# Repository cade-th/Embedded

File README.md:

# Kitchen Timer: Embedded Systems Project

Cade Thornton

10/23/2023

Embedded Systems

## Table of Contents

-------

+ [Introduction](#Introduction )
+ [PCB Design in KiCad](#PCBDesigninKiCad)
    * [Schematic](#Schematic)
    * [Layout](#Layout)

+ [Arduino Code](#ArduinoCode)
    * [Overview](#Overview)

+ [Conclusion](#Conclusion)

## Introduction 

-------

The goal of this project is to create a PCB schematic and layout for a simple kitchen timer made using the AT-mega microprocessor, the Arduino IDE, and KiCad.

<div align="center">
  <p style="font-size: small;">
    Figure 1 (Completed PCB board setup)
  </p>
</div>

## PCB design in KiCad

### Schematic
<p align="center"> 
The schematic for this design included roughly nine modules that work fit together to make the full system.
</p>

<div align="center">
  <p style="font-size: small;">
    Figure 2 (entire schematic PCB system)
  </p>
</div>

### Layout 

<p align="center"> 
The layout for this design was created after finishing the schematic design. 
</p>

<div align="center">
  <p style="font-size: small;">
    Figure 2 (entire layout of the PCB system)
  </p>
</div>

------

## Arduino Code

The code used to program the kitchen timer can be found in the /ArduinoCode folder.

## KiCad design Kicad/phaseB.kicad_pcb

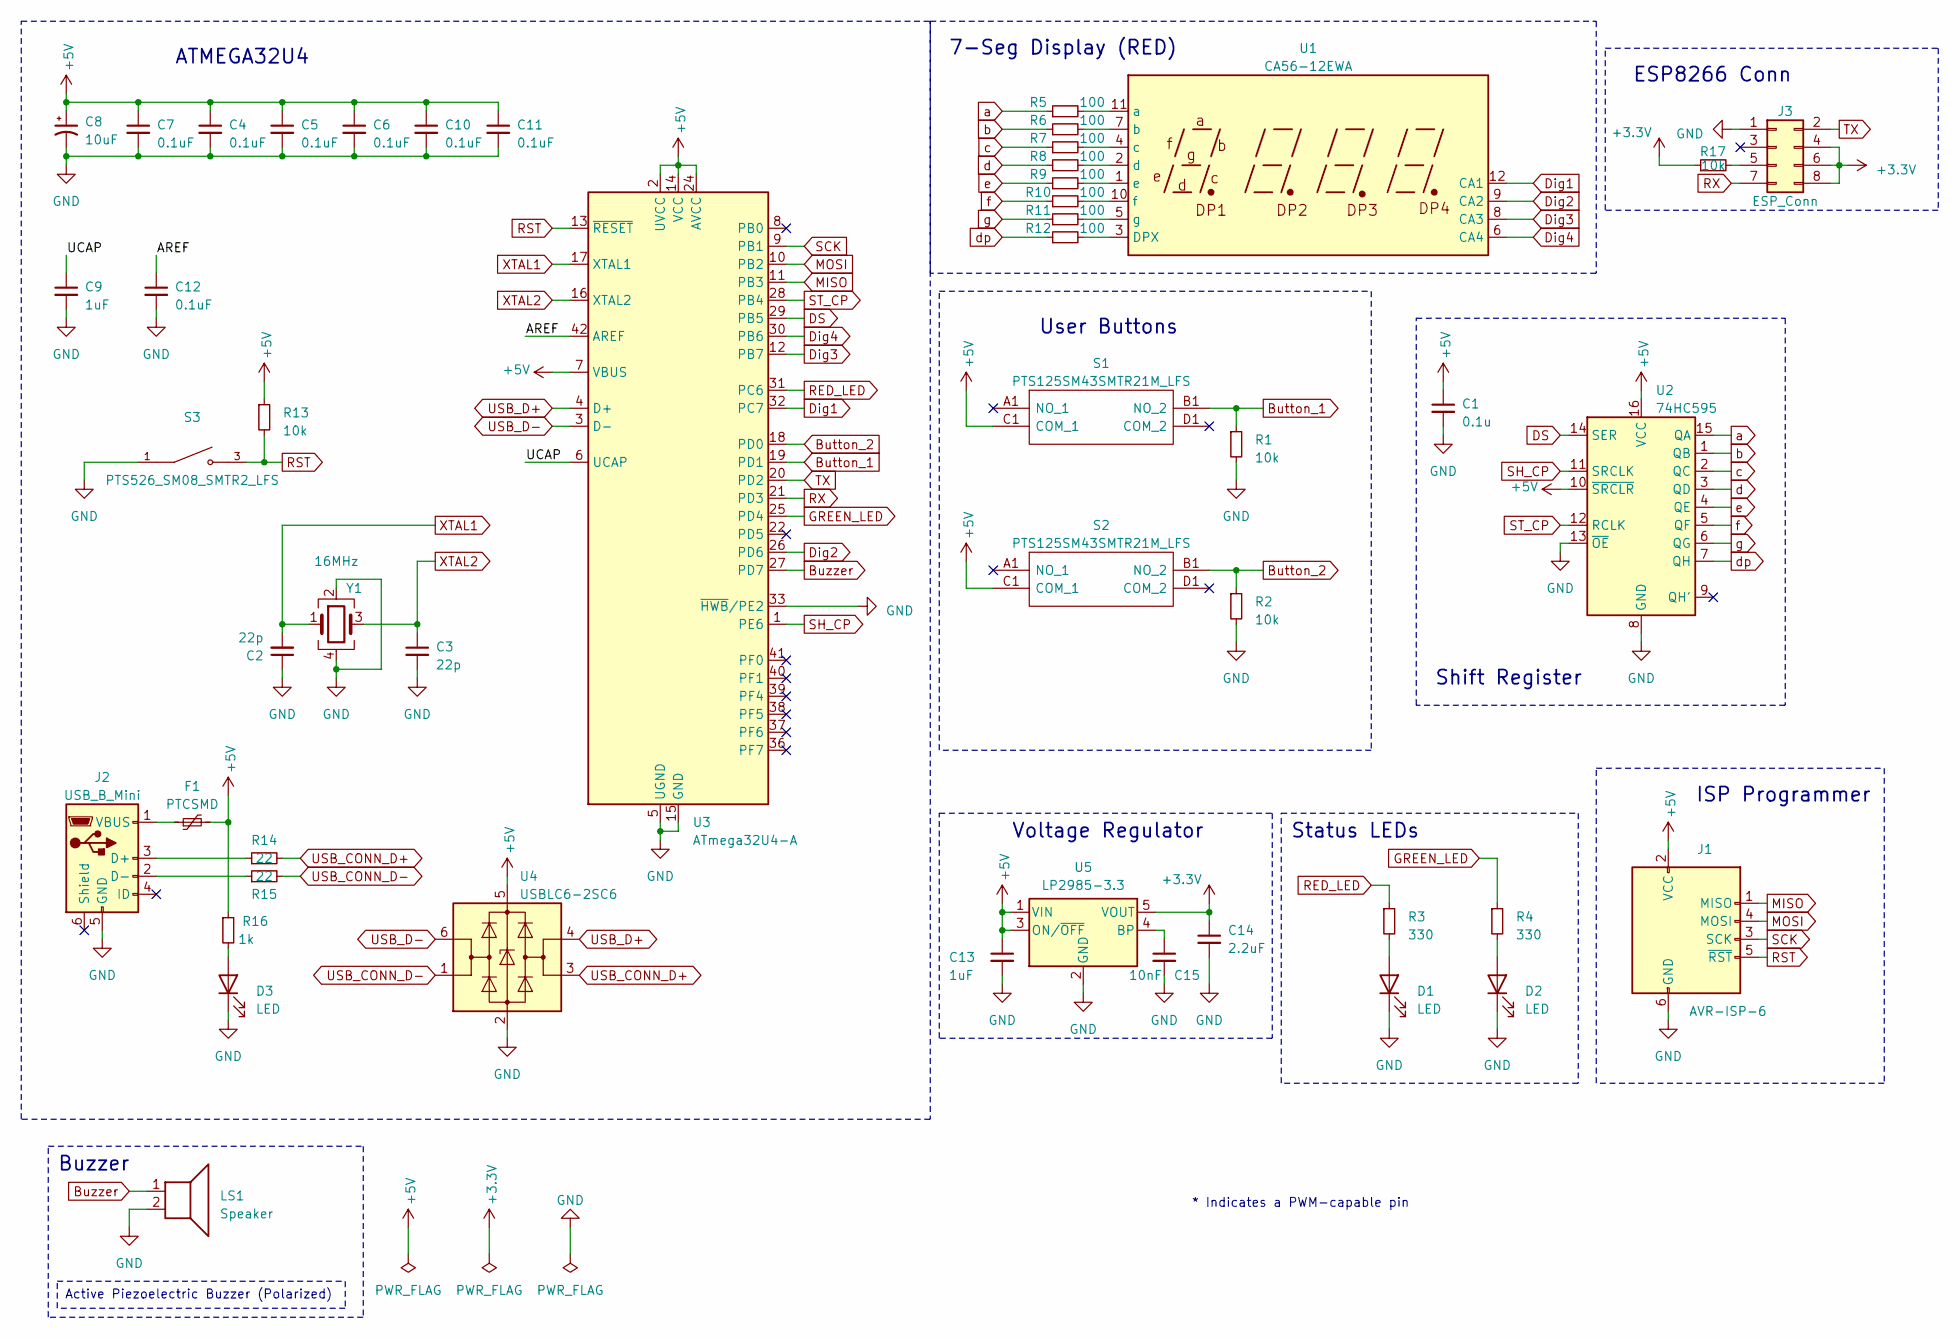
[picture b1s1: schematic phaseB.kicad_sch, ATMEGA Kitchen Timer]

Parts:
C1: 0.1u; C_0603_1608Metric
C2, C3: 22p; C_0603_1608Metric
C4, C5, C6, C7, C10, C11, C12: 0.1uF; C_0603_1608Metric
C8: 10uF; C_0805_2012Metric
C9, C13: 1uF; C_0603_1608Metric
C14: 2.2uF; C_0603_1608Metric
C15: 10nF; C_0603_1608Metric
D1, D2, D3: LED; LED_0805_2012Metric
F1: PTCSMD; Fuse_1812_4532Metric
J1: AVR-ISP-6; PinSocket_2x03_P2.54mm_Vertical
J2: USB_B_Mini; USB_Mini-B_Lumberg_2486_01_Horizontal
J3: ESP_Conn; PinSocket_2x04_P2.54mm_Vertical
LS1: Speaker; Buzzer_12x9.5RM7.6
R1, R2: 10k; R_0805_2012Metric
R3, R4: 330; R_0805_2012Metric
R5, R6, R7, R8, R9, R10, R11, R12: 100; R_0805_2012Metric
R13, R17: 10k; R_0603_1608Metric
R14, R15: 22; R_0603_1608Metric
R16: 1k; R_0603_1608Metric
S1, S2: PTS125SM43SMTR21M_LFS; PTS125_SMD_Button; Manufacturer_Part_Number PTS125SM43SMTR21M LFS; Mouser Part Number 611-PTS125S43SMTRLFS
S3: PTS526_SM08_SMTR2_LFS; PTS526_SMD_Button; PARTREV 20 mar 19
U1: CA56-12EWA
U2: 74HC595; TSSOP-16_4.4x5mm_P0.65mm
U3: ATmega32U4-A; TQFP-44_10x10mm_P0.8mm
U4: USBLC6-2SC6; SOT-23-6
U5: LP2985-3.3; SOT-23-5
Y1: 16MHz; Crystal_SMD_Abracon_ABM8G-4Pin_3.2x2.5mm

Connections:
+3.3V: C14.1, J3.4, J3.6, J3.8, R17.1, U5.5 (VOUT)
+5V: C1.1, C4.1, C5.1, C6.1, C7.1, C8.1, C10.1, C11.1, C13.1, F1.2, J1.2 (VCC), R13.1, R16.1, S1.C1 (COM_1), S2.C1 (COM_1), U2.10 (~SRCLR), U2.16 (VCC), U3.2 (UVCC), U3.7 (VBUS), U3.14 (VCC), U3.24 (AVCC), U3.34 (VCC), U3.44 (AVCC), U4.5 (VBUS), U5.1 (VIN), U5.3 (ON/~OFF)
/AREF: C12.1, U3.42 (AREF)
/UCAP: C9.1, U3.6 (UCAP)
Button_1: R1.1, S1.B1 (NO_2), U3.19 (PD1)
Button_2: R2.1, S2.B1 (NO_2), U3.18 (PD0)
Buzzer: LS1.1, U3.27 (PD7)
DS: U2.14 (SER), U3.29 (PB5)
Dig1: U1.12 (CA1), U3.32 (PC7)
Dig2: U1.9 (CA2), U3.26 (PD6)
Dig3: U1.8 (CA3), U3.12 (PB7)
Dig4: U1.6 (CA4), U3.30 (PB6)
GND: C1.2, C2.1, C3.2, C4.2, C5.2, C6.2, C7.2, C8.2, C9.2, C10.2, C11.2, C12.2, C13.2, C14.2, C15.2, D1.1 (K), D2.1 (K), D3.1 (K), J1.6 (GND), J2.5 (GND), J3.1, LS1.2, R1.2, R2.2, S3.1, U2.8 (GND), U2.13 (~OE), U3.5 (UGND), U3.15 (GND), U3.23 (GND), U3.33 (~HWB/PE2), U3.35 (GND), U3.43 (GND), U4.2 (GND), U5.2 (GND), Y1.2, Y1.4
GREEN_LED: R4.1, U3.25 (PD4)
MISO: J1.1 (MISO), U3.11 (PB3)
MOSI: J1.4 (MOSI), U3.10 (PB2)
unnamed: D1.2 (A), R3.2
unnamed: D2.2 (A), R4.2
unnamed: D3.2 (A), R16.2
unnamed: J2.3 (D+), R14.1
unnamed: J2.2 (D-), R15.1
unnamed: F1.1, J2.1 (VBUS)
unnamed: J3.5, R17.2
unnamed: R12.2, U1.3 (DPX)
unnamed: R5.2, U1.11 (a)
unnamed: R6.2, U1.7 (b)
unnamed: R7.2, U1.4 (c)
unnamed: R8.2, U1.2 (d)
unnamed: R9.2, U1.1 (e)
unnamed: R10.2, U1.10 (f)
unnamed: R11.2, U1.5 (g)
unnamed: C15.1, U5.4 (BP)
RED_LED: R3.1, U3.31 (PC6)
RST: J1.5 (~RST), R13.2, S3.3, U3.13 (~RESET)
RX: J3.7, U3.21 (PD3)
SCK: J1.3 (SCK), U3.9 (PB1)
SH_CP: U2.11 (SRCLK), U3.1 (PE6)
ST_CP: U2.12 (RCLK), U3.28 (PB4)
TX: J3.2, U3.20 (PD2)
USB_CONN_D+: R14.2, U4.3 (I/O2)
USB_CONN_D-: R15.2, U4.1 (I/O1)
USB_D+: U3.4 (D+), U4.4 (I/O2)
USB_D-: U3.3 (D-), U4.6 (I/O1)
XTAL1: C2.2, U3.17 (XTAL1), Y1.1
XTAL2: C3.1, U3.16 (XTAL2), Y1.3
a: R5.1, U2.15 (QA)
b: R6.1, U2.1 (QB)
c: R7.1, U2.2 (QC)
d: R8.1, U2.3 (QD)
dp: R12.1, U2.7 (QH)
e: R9.1, U2.4 (QE)
f: R10.1, U2.5 (QF)
g: R11.1, U2.6 (QG)

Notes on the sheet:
Active Piezoelectric Buzzer (Polarized)
Shift Register
Voltage Regulator
Status LEDs
ATMEGA32U4
User Buttons
Buzzer
* Indicates a PWM-capable pin
7-Seg Display (RED)
ISP Programmer
ESP8266 Conn

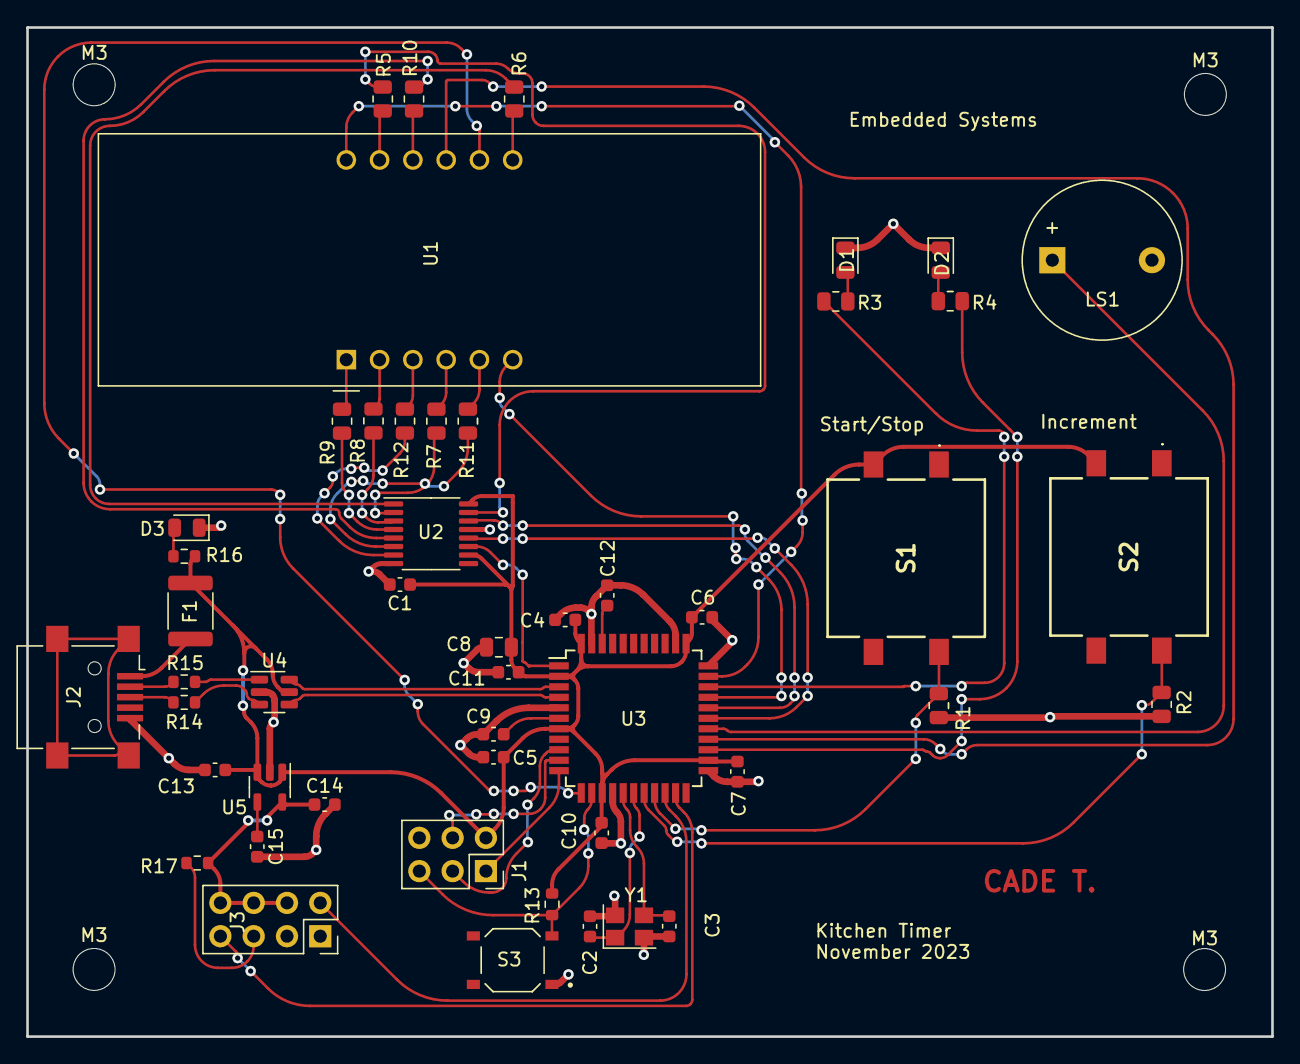
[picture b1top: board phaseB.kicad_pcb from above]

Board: 2 copper layers, 95.0 x 77.0 mm, 53 parts (0 on the bottom side), 53 nets.

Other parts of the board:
M3, M3#2, M3#3, M3#4: MountingHole_3.2mm_M3

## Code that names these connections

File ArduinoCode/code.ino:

#include <Arduino.h>
#include <avr/power.h>
#include <Arduino_FreeRTOS.h>
// macros
#define PF0   A5
#define PF1   A4
#define PF4   A3
#define PF5   A2
#define PF6   A1
#define PF7   A0
#define DIGIT_1   13  // PC7
#define RED_LED   5   // PC6
#define DIGIT_4   10  // PB6
#define DATA      9   // PB5 
#define LATCH     8   // PB4 
#define BUZZER    6   // PD7
#define DIGIT_2   12  // PD6
#define GREEN_LED 4   // PD4
#define PD3       1   // TX
#define PD2       0   // RX
#define BUTTON_1  2   // PD1 Start/Stop Timer and Stop Buzzer 
#define BUTTON_2  3   // PD0 Inc Timer
#define DIGIT_3   11  // PB7

//7-Seg Display Variables
unsigned char gTable[]=
{0x3f,0x06,0x5b,0x4f,0x66,0x6d,0x7d,0x07,0x7f,0x6f,0x77,0x7c
,0x39,0x5e,0x79,0x71,0x00};

//Timer Variables
#define DEFAULT_COUNT 30 //s
int  gCount = DEFAULT_COUNT;
char gBuzzerFlag = 0;
unsigned char gTimerRunning = 0;
//define task handles
TaskHandle_t TaskClockTimer_Handler;

void setup() {

  if(F_CPU == 16000000) clock_prescale_set(clock_div_1);

   pinMode(RED_LED, OUTPUT);
   pinMode(GREEN_LED, OUTPUT);
   //LEDs
   digitalWrite(RED_LED, HIGH);
   digitalWrite(GREEN_LED, HIGH);
   pinMode(BUTTON_1, INPUT);
   pinMode(BUTTON_2, INPUT);
   pinMode(BUZZER, OUTPUT);
   //default buzzer 
   digitalWrite(BUZZER,LOW);
   //7-Seg Display
   pinMode(DIGIT_1, OUTPUT);
   pinMode(DIGIT_2, OUTPUT);
   pinMode(DIGIT_3, OUTPUT);
   pinMode(DIGIT_4, OUTPUT);
   //Shift Register Pins
   pinMode(LATCH, OUTPUT);
   pinMode(CLOCK, OUTPUT);
   pinMode(DATA, OUTPUT);
   dispOff();

  //7-Seg Display Task
  xTaskCreate(TaskDisplay, "Display", 128,NULL,0,NULL);
  //Clock timer Task
  xTaskCreate(TaskClockTimer, "ClockTimer", 128, NULL, 0,&TaskClockTimer_Handler);
  stopTaskClockTimer();
  //Buzzer Task
  xTaskCreate(TaskBuzzer,"Buzzer",128, NULL, 0,NULL );
  //Read Button 2 Task
  xTaskCreate(TaskReadButton2,"ReadButton2", 128,NULL, 0,NULL);
  //Read Button 1 Task
  xTaskCreate(TaskReadButton1,"ReadButton1",128,  NULL, 0,NULL);
}

void loop() {}
/*
7-Seg Display Task
*/
void TaskDisplay(void * pvParameters) {
  (void) pvParameters;
  byte current_digit;
  for (;;) {
    dispOff();
    switch (current_digit){
      case 1: //0x:xx
        display( int((gCount/60) / 10) % 6, 0 );   // prepare to display digit 1 (most left)
        digitalWrite(DIGIT_1, LOW);  // turn on digit 1
        break;
      case 2: //x0:xx
        display( int(gCount / 60) % 10, 1 );   // prepare to display digit 2
        digitalWrite(DIGIT_2, LOW);     // turn on digit 2
        break;
      case 3: //xx:0x
        display( (gCount / 10) % 6, 0 );   // prepare to display digit 3
        digitalWrite(DIGIT_3, LOW);    // turn on digit 3
        break;
      case 4: //xx:x0
        display(gCount % 10, 0); // prepare to display digit 4 (most right)
        digitalWrite(DIGIT_4, LOW);  // turn on digit 4
    }
    current_digit = (current_digit % 4) + 1;
    vTaskDelay( 5 / portTICK_PERIOD_MS );
  }
}

/*
Clock Timer Task
*/
void TaskClockTimer(void *pvParameters) {
  (void) pvParameters;
  for (;;) {
    gCount--;
    if(gCount == 0) { 
      gBuzzerFlag = 1;
      gTimerRunning = 0;
      stopTaskClockTimer();
    }
    vTaskDelay( 1000 / portTICK_PERIOD_MS );
  }
}

/* 
Buzzer Task 
*/
void TaskBuzzer(void *pvParameters) {
  (void) pvParameters;
  unsigned char state = 0;
  for (;;) {
    if(gBuzzerFlag == 1) {      
      digitalWrite(RED_LED, HIGH);
      digitalWrite(GREEN_LED, LOW);
      digitalWrite(BUZZER, HIGH);
      vTaskDelay( 250 / portTICK_PERIOD_MS );
      digitalWrite(BUZZER, LOW);
      vTaskDelay( 250 / portTICK_PERIOD_MS );
    }
    else
      digitalWrite(BUZZER, LOW);
    vTaskDelay(1);
  }
}
/*
Read Button 2 Task
*/
void TaskReadButton2(void *pvParameters) {
  (void) pvParameters;
  unsigned int buttonState = 0; //reading push button status flag
  for (;;) { 
    //Read Button 2
    buttonState = digitalRead(BUTTON_2);
    if(buttonState == 1) {
      vTaskDelay( 250 / portTICK_PERIOD_MS );
      gCount++;
    }
    vTaskDelay(1);
  }
}
/*
Read Button 1 Task
*/
void TaskReadButton1(void *pvParameters) {
  (void) pvParameters;
  unsigned int buttonState = 0;
  for (;;)
  { 
    buttonState = digitalRead(BUTTON_1);
    if(buttonState == 1) {
      vTaskDelay( 250 / portTICK_PERIOD_MS );
      if(gTimerRunning == 0) {
        gTimerRunning = 1;
        if(gCount == 0) {
          gCount = DEFAULT_COUNT;
        }
        if(gBuzzerFlag == 1) {
          gBuzzerFlag = 0;
          digitalWrite(RED_LED, HIGH);
          digitalWrite(GREEN_LED, HIGH);
        }
        else {
          startTaskClockTimer();
          digitalWrite(RED_LED, LOW);
          digitalWrite(GREEN_LED, HIGH);
        }
      }
      else {
        stopTaskClockTimer();
        gTimerRunning = 0;
        digitalWrite(RED_LED, HIGH);
        digitalWrite(GREEN_LED, HIGH);
      }
    }
    vTaskDelay(1);
  }
}
void stopClockTimer() {
  vTaskSuspend(TaskClockTimer_Handler);
}
void startClockTimer() {
  vTaskResume(TaskClockTimer_Handler);
}
void dispOff() {
   digitalWrite(DIGIT_1, HIGH);
   digitalWrite(DIGIT_2, HIGH);
   digitalWrite(DIGIT_3, HIGH);
   digitalWrite(DIGIT_4, HIGH);
}
void display(unsigned char num, unsigned char dp) {
  digitalWrite(LATCH, LOW);
  shiftOut(DATA, CLOCK, MSBFIRST, gTable[num] | (dp<<7));
  digitalWrite(LATCH, HIGH);
}

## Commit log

2023-11-06 emb
    layout and stuff
2023-11-06 embedded
    hi
2023-11-06 e
    e
